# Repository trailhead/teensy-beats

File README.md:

# teensy-beats
Teensy Beats Shield

An all-in-one, made to hack step sequencer built around the Teensy platform with LiPo charging, touch TFT, encoders, buttons, and RGB leds.

Project build log and photos here:
https://hackaday.io/project/161127-teensy-beats-shield

...

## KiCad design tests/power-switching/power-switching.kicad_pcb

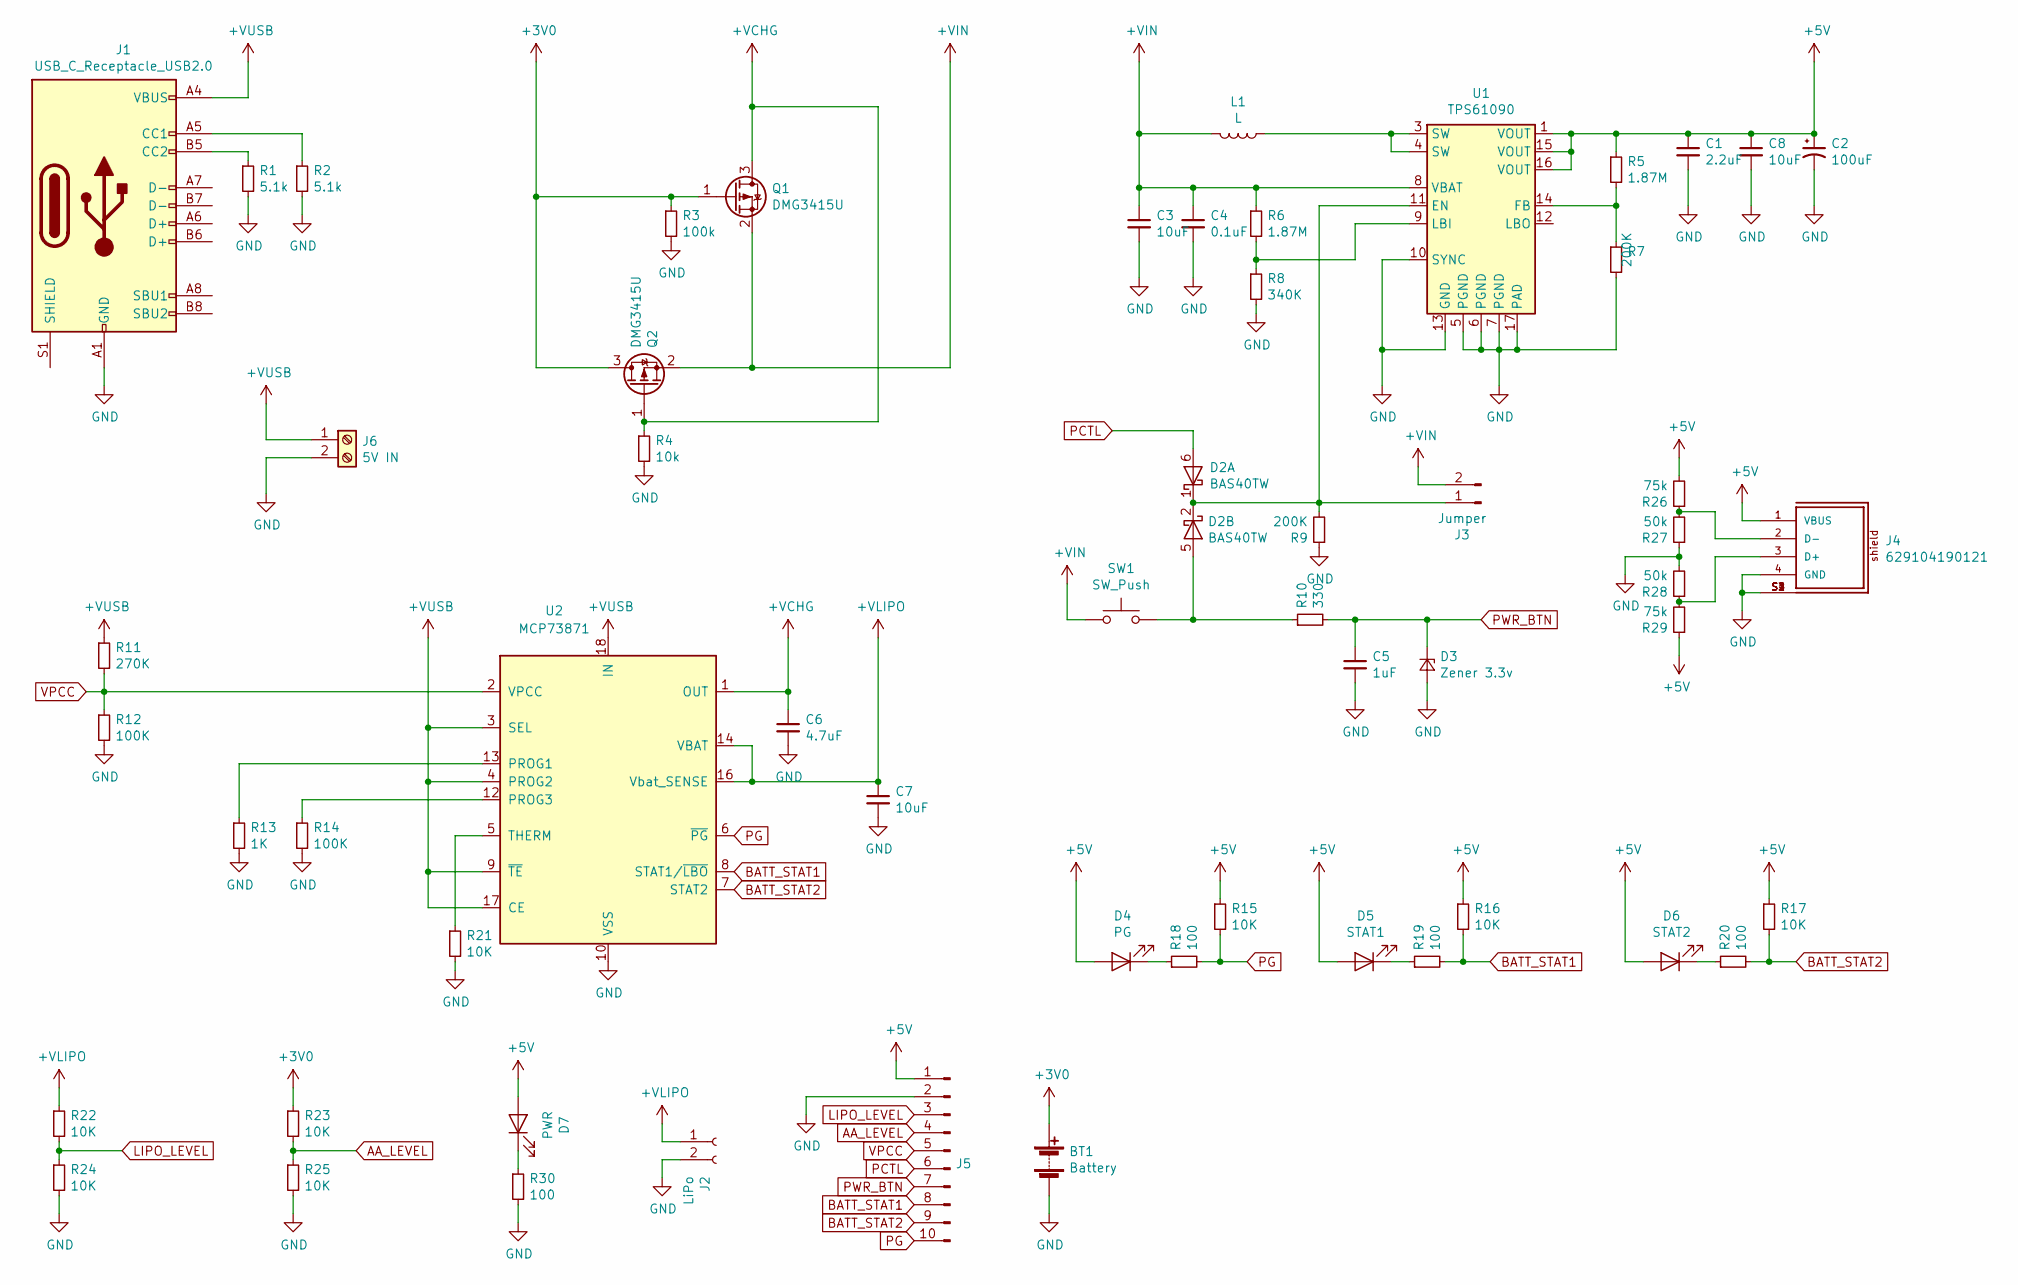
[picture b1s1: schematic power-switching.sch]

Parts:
BT1: Battery; BatteryHolder_Keystone_2462_2xAA
C1: 2.2uF; C_0805_2012Metric
C2: 100uF; CP_Elec_5x5.3
C3, C8: 10uF; C_1206_3216Metric
C4: 0.1uF; C_0805_2012Metric
C5: 1uF; C_0805_2012Metric
C6: 4.7uF; C_0805_2012Metric
C7: 10uF; C_0805_2012Metric
D2: BAS40TW; SOT-363_SC-70-6
D3: Zener 3.3v; D_SOD-323_HandSoldering
D4: PG; LED_0805_2012Metric
D5: STAT1; LED_0805_2012Metric
D6: STAT2; LED_0805_2012Metric
D7: PWR; LED_0805_2012Metric
J1: USB_C_Receptacle_USB2.0; MOLEX_105450-0101
J2: LiPo; JST_PH_S2B-PH-SM4-TB_1x02-1MP_P2.00mm_Horizontal
J3: Jumper; PinHeader_1x02_P2.54mm_Vertical
J4: 629104190121; PART-NUMBER 629104190121
J5: Conn_01x10_Male; PinHeader_1x10_P2.54mm_Vertical
J6: 5V IN; PhoenixContact_MSTBA_2,5_2-G_1x02_P5.00mm_Horizontal
L1: L; L_Taiyo-Yuden_NR-60xx
Q1, Q2: DMG3415U; SOT-23
R1, R2: 5.1k; R_0805_2012Metric
R3: 100k; R_0805_2012Metric
R4: 10k; R_0805_2012Metric
R5, R6: 1.87M; R_0805_2012Metric
R7, R9: 200K; R_0805_2012Metric
R8: 340K; R_0805_2012Metric
R10: 330; R_0805_2012Metric
R11: 270K; R_0805_2012Metric
R12, R14: 100K; R_0805_2012Metric
R13: 1K; R_0805_2012Metric
R15, R16, R17, R21, R22, R23, R24, R25: 10K; R_0805_2012Metric
R18, R19, R20, R30: 100; R_0805_2012Metric
R26, R29: 75k; R_0805_2012Metric
R27, R28: 50k; R_0805_2012Metric
SW1: SW_Push; SW_Tactile_SKHH_Angled
U1: TPS61090; QFN-16-1EP_4x4mm_P0.65mm_EP2.7x2.7mm_ThermalVias
U2: MCP73871; QFN-20-1EP_4x4mm_P0.5mm_EP2.6x2.6mm_ThermalVias

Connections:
+3V0: BT1.1 (+), Q1.1 (G), Q2.3 (D), R3.1, R23.1
+5V: C1.1, C2.1, C8.1, D4.2 (A), D5.2 (A), D6.2 (A), D7.2 (A), J4.1 (VBUS), J5.1, R5.1, R15.1, R16.1, R17.1, R26.2, R29.1, U1.1 (VOUT), U1.15 (VOUT), U1.16 (VOUT)
+VCHG: C6.1, Q1.3 (D), Q2.1 (G), R4.1, U2.1 (OUT), U2.20 (OUT)
+VIN: C3.1, C4.1, J3.2, L1.2, Q1.2 (S), Q2.2 (S), R6.1, SW1.2, U1.8 (VBAT)
+VLIPO: C7.1, J2.1, R22.1, U2.14 (VBAT), U2.15 (VBAT), U2.16 (Vbat_SENSE)
+VUSB: J1.A4 (VBUS), J1.A9 (VBUS), J1.B4 (VBUS), J1.B9 (VBUS), J6.1, R11.1, U2.3 (SEL), U2.4 (PROG2), U2.9 (~TE), U2.17 (CE), U2.18 (IN), U2.19 (IN)
AA_LEVEL: J5.4, R23.2, R25.1
BATT_STAT1: J5.8, R16.2, R19.2, U2.8 (STAT1/~LBO~)
BATT_STAT2: J5.9, R17.2, R20.2, U2.7 (STAT2)
GND: BT1.2 (-), C1.2, C2.2, C3.2, C4.2, C5.2, C6.2, C7.2, C8.2, D3.2 (A), J1.A1 (GND), J1.A12 (GND), J1.B1 (GND), J1.B12 (GND), J2.2, J4.4 (GND), J4.S1, J4.S2, J4.S3, J4.S4, J5.2, J6.2, R1.2, R2.2, R3.2, R4.2, R7.2, R8.2, R9.1, R12.2, R13.2, R14.2, R21.2, R24.2, R25.2, R27.1, R28.2, R30.2, U1.5 (PGND), U1.6 (PGND), U1.7 (PGND), U1.10 (SYNC), U1.13 (GND), U1.17 (PAD), U2.10 (VSS), U2.11 (VSS), U2.21 (VSS)
LIPO_LEVEL: J5.3, R22.2, R24.1
unnamed: D2.1 (K), D2.2 (K), J3.1, R9.2, U1.11 (EN)
unnamed: D2.5 (A), R10.1, SW1.1
unnamed: D4.1 (K), R18.1
unnamed: D5.1 (K), R19.1
unnamed: D6.1 (K), R20.1
unnamed: D7.1 (K), R30.1
unnamed: J1.A5 (CC1), R2.1
unnamed: J1.B5 (CC2), R1.1
unnamed: J4.2 (D-), R26.1, R27.2
unnamed: J4.3 (D+), R28.1, R29.2
unnamed: L1.1, U1.3 (SW), U1.4 (SW)
unnamed: R5.2, R7.1, U1.14 (FB)
unnamed: R6.2, R8.1, U1.9 (LBI)
unnamed: R13.1, U2.13 (PROG1)
unnamed: R14.1, U2.12 (PROG3)
unnamed: R21.1, U2.5 (THERM)
PCTL: D2.6 (A), J5.6
PG: J5.10, R15.2, R18.2, U2.6 (~PG~)
PWR_BTN: C5.1, D3.1 (K), J5.7, R10.2
VPCC: J5.5, R11.2, R12.1, U2.2 (VPCC)

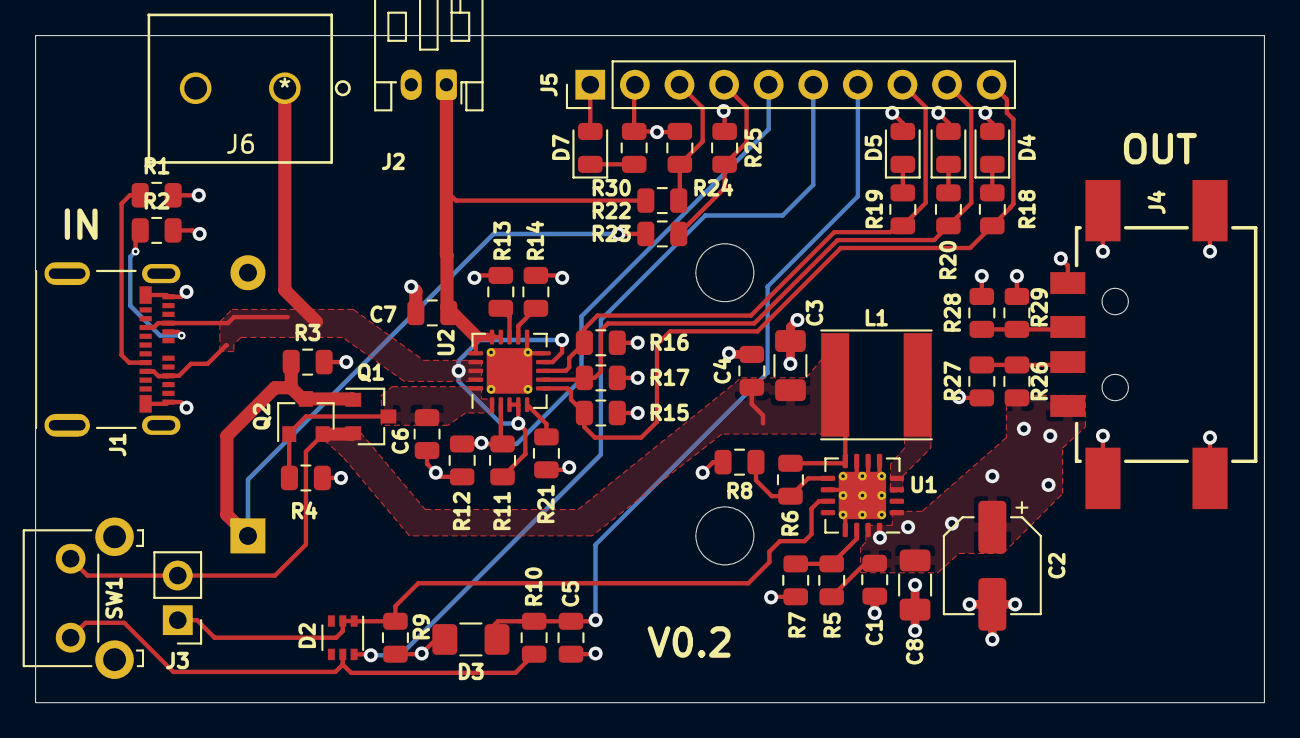
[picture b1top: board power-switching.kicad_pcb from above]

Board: 4 copper layers, 70.0 x 38.0 mm, 57 parts (1 on the bottom side), 31 nets.

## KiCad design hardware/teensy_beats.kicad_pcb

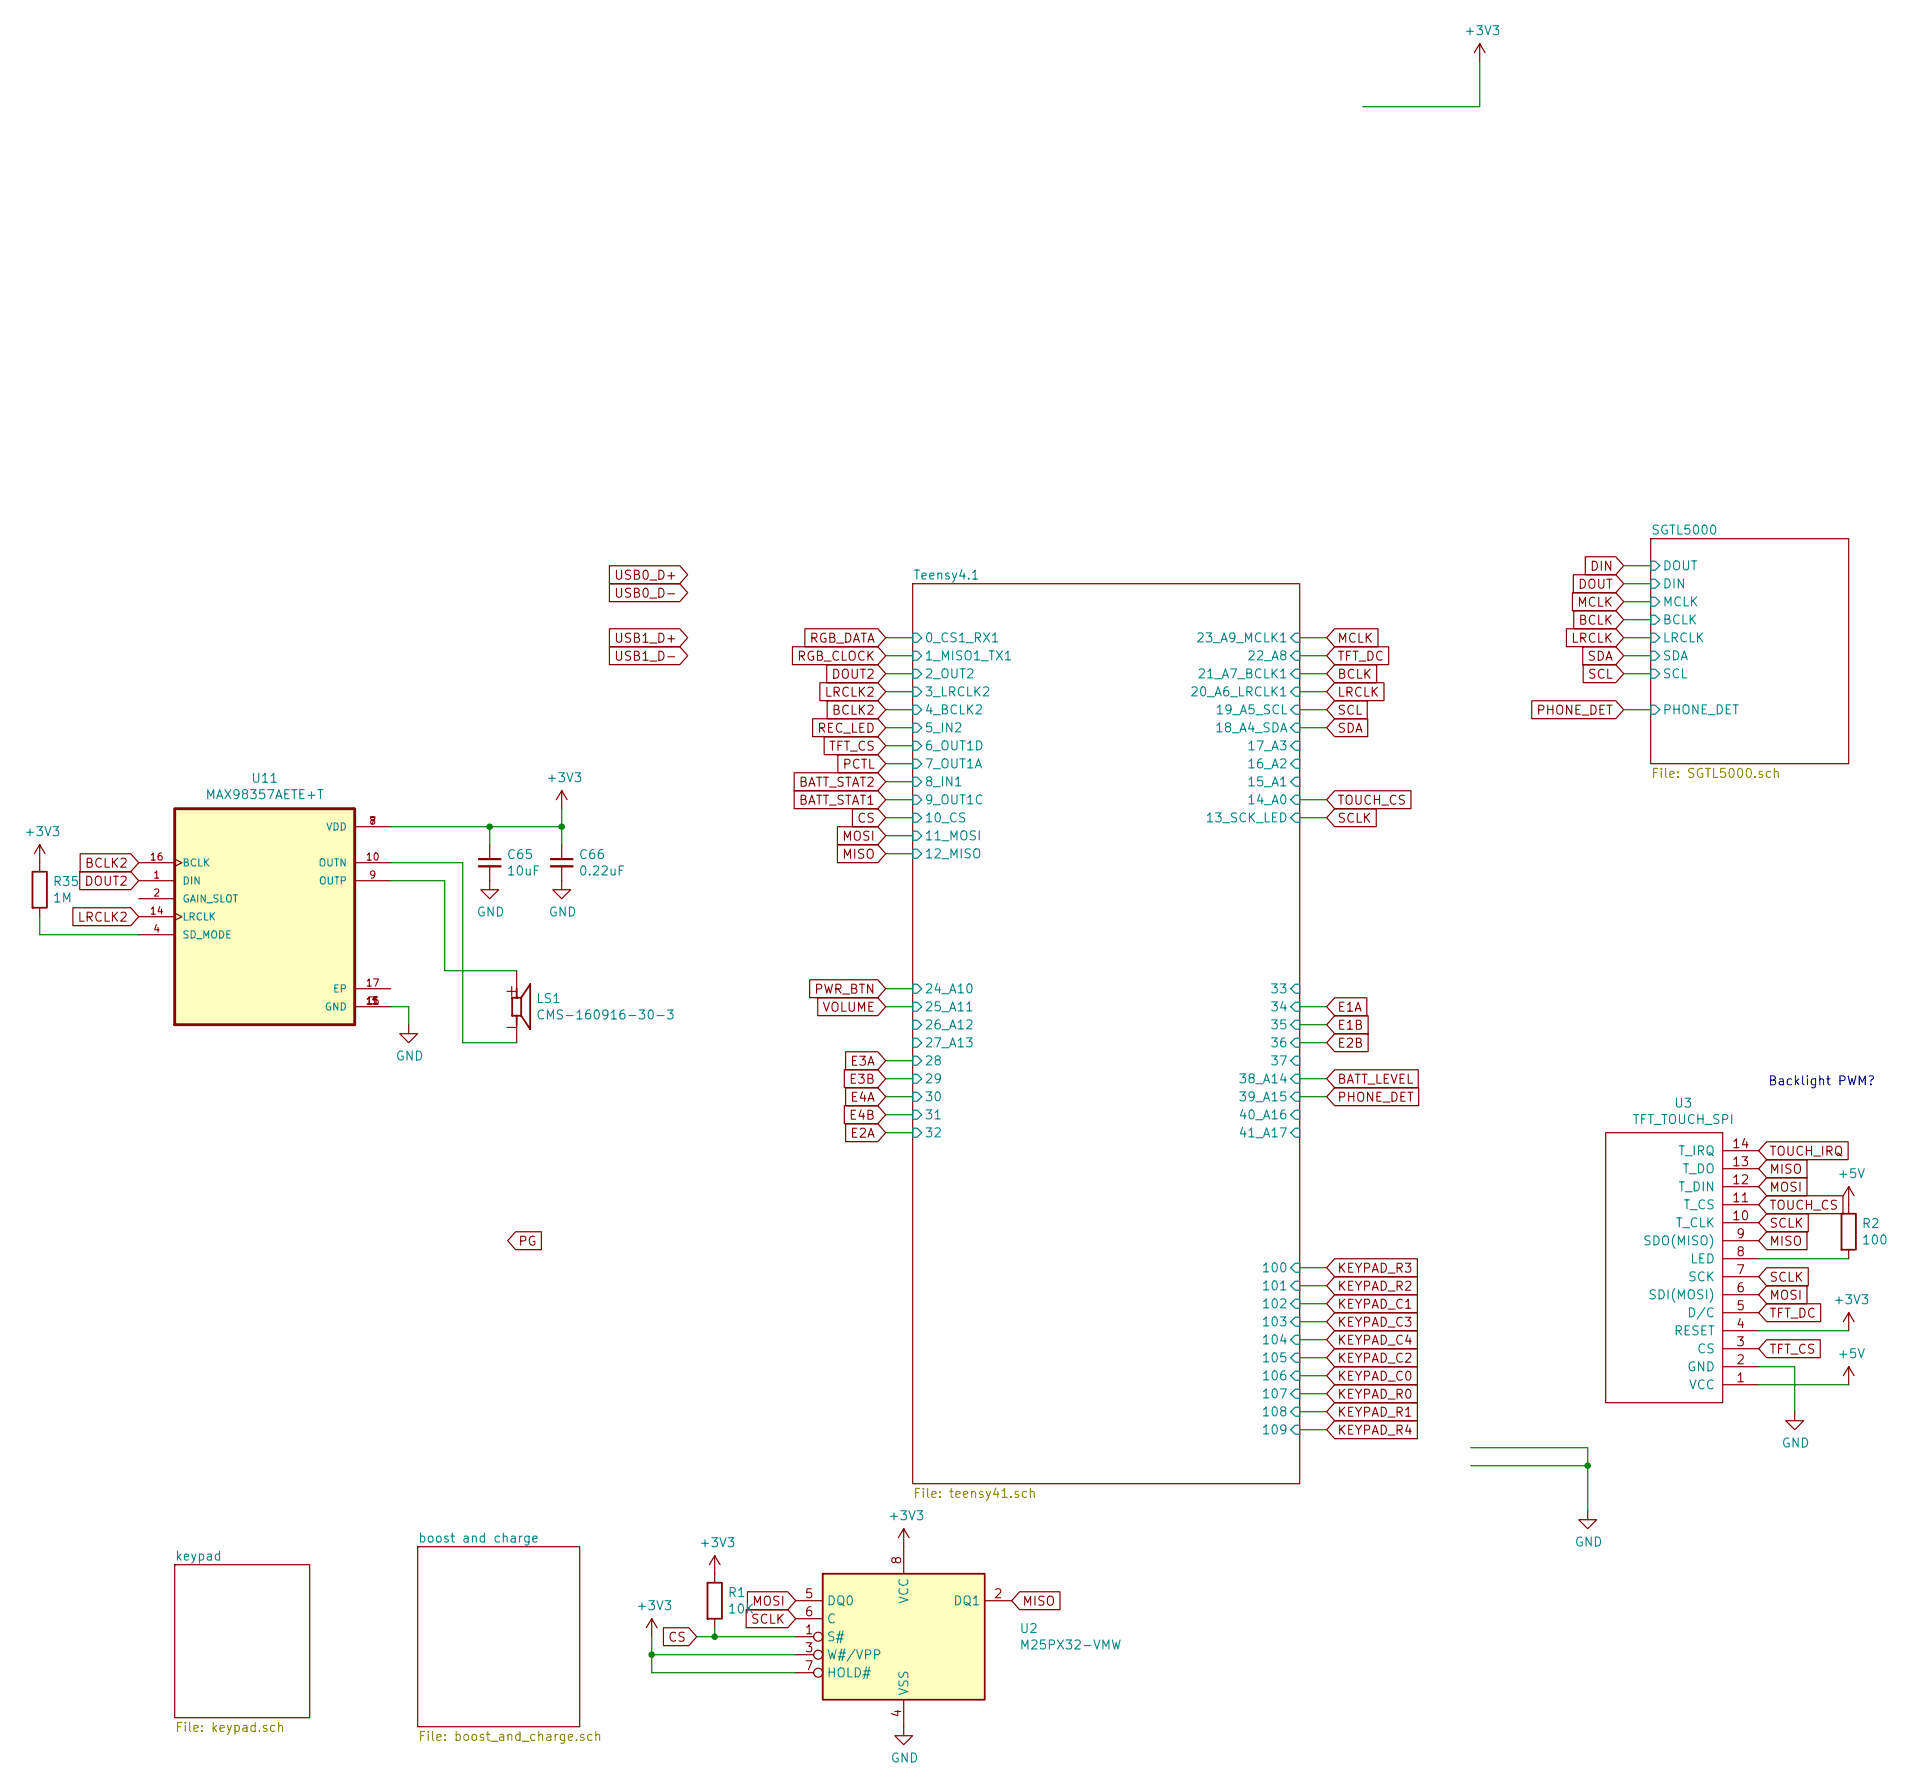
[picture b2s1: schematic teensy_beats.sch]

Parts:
C65: 10uF; C_0603_1608Metric
C66: 0.22uF; C_0402_1005Metric
LS1: CMS-160916-30-3; SPKR_CMS-160916-30-3; PARTREV 1.01
R1: 10K; R_0402_1005Metric
R2: 100; R_0402_1005Metric
R35: 1M; R_0402_1005Metric
U2: M25PX32-VMW; SOIC-8-N
U3: TFT_TOUCH_SPI; 2.4inTFT_TOUCH_SPI
U11: MAX98357AETE+T; QFN50P300X300X80-17N

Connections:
+3V3: C65.1, C66.1, R1.1, R35.1, U2.3 (W#/VPP), U2.7 (HOLD#), U2.8 (VCC), U3.4 (RESET), U11.7 (VDD), U11.8 (VDD); also elsewhere on the board
+5V: R2.1, U3.1 (VCC); also elsewhere on the board
BCLK2: U11.16 (BCLK); also elsewhere on the board
CS: R1.2, U2.1 (S#); also elsewhere on the board
DOUT2: U11.1 (DIN); also elsewhere on the board
GND: C65.2, C66.2, U2.4 (VSS), U3.2 (GND), U11.3 (GND), U11.11 (GND), U11.15 (GND); also elsewhere on the board
LRCLK2: U11.14 (LRCLK); also elsewhere on the board
MISO: U2.2 (DQ1), U3.9 (SDO(MISO)), U3.13 (T_DO); also elsewhere on the board
MOSI: U2.5 (DQ0), U3.6 (SDI(MOSI)), U3.12 (T_DIN); also elsewhere on the board
unnamed: LS1.N, U11.10 (OUTN)
unnamed: LS1.P, U11.9 (OUTP)
unnamed: R2.2, U3.8 (LED)
unnamed: R35.2, U11.4 (SD_MODE)
SCLK: U2.6 (C), U3.7 (SCK), U3.10 (T_CLK); also elsewhere on the board
TFT_CS: U3.3 (CS); also elsewhere on the board
TFT_DC: U3.5 (D/C); also elsewhere on the board
TOUCH_CS: U3.11 (T_CS); also elsewhere on the board
TOUCH_IRQ: U3.14 (T_IRQ)

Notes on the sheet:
Backlight PWM?

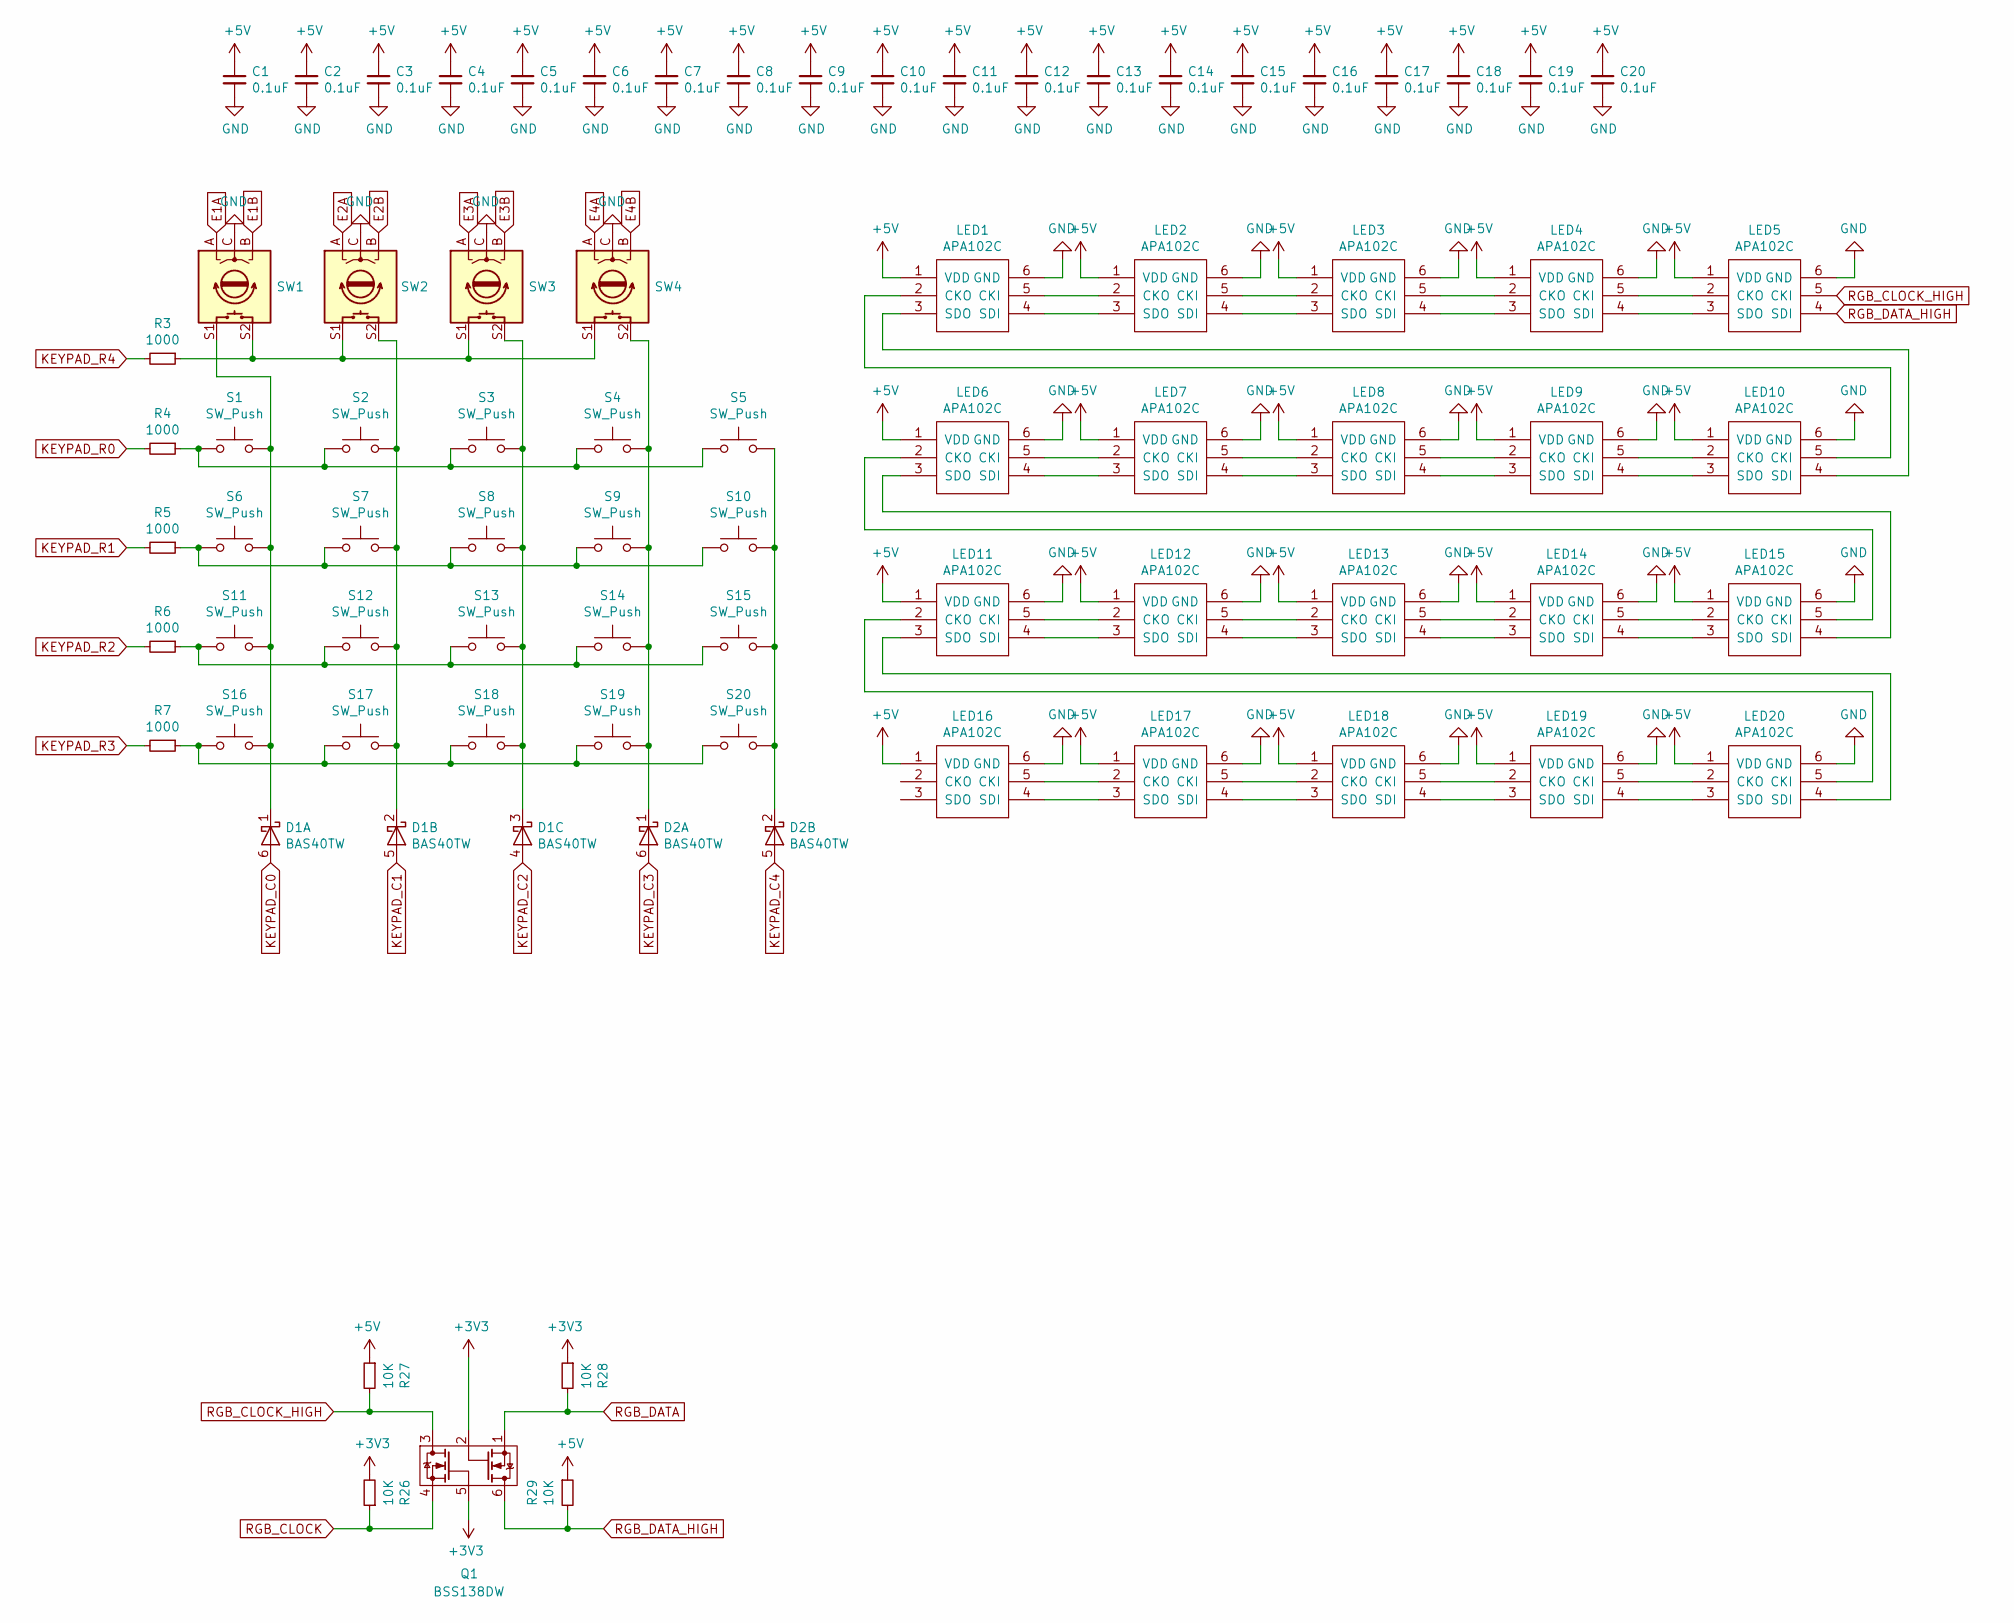
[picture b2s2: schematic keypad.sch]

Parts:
C1, C2, C3, C4, C5, C6, C7, C8, C9, C10, C11, C12, C13, C14, C15, C16, C17, C18, C19, C20: 0.1uF; C_0402_1005Metric
D1, D2: BAS40TW; SOT-363_SC-70-6
LED1, LED2, LED3, LED4, LED5, LED6, LED7, LED8, LED9, LED10, LED11, LED12, LED13, LED14, LED15, LED16, LED17, LED18, LED19, LED20: APA102C; APA102C-2020
Q1: BSS138DW; SOT-363_SC-70-6
R3, R4, R5, R6, R7: 1000; R_0402_1005Metric
R26, R27, R28, R29: 10K; R_0402_1005Metric
S1, S2, S3, S4, S5, S6, S7, S8, S9, S10, S11, S12, S13, S14, S15, S16, S17, S18, S19, S20: SW_Push; SW_SPST_EVQQ2
SW1, SW2, SW3, SW4: Rotary_Encoder_Switch; Bourns-SMD-Encoder

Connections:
+3V3: Q1.2 (G1), Q1.5 (G2), R26.2, R28.1; also elsewhere on the board
+5V: C1.1, C2.1, C3.1, C4.1, C5.1, C6.1, C7.1, C8.1, C9.1, C10.1, C11.1, C12.1, C13.1, C14.1, C15.1, C16.1, C17.1, C18.1, C19.1, C20.1, LED1.1 (VDD), LED2.1 (VDD), LED3.1 (VDD), LED4.1 (VDD), LED5.1 (VDD), LED6.1 (VDD), LED7.1 (VDD), LED8.1 (VDD), LED9.1 (VDD), LED10.1 (VDD), LED11.1 (VDD), LED12.1 (VDD), LED13.1 (VDD), LED14.1 (VDD), LED15.1 (VDD), LED16.1 (VDD), LED17.1 (VDD), LED18.1 (VDD), LED19.1 (VDD), LED20.1 (VDD), R27.1, R29.1; also elsewhere on the board
E1A: SW1.A; also elsewhere on the board
E1B: SW1.B; also elsewhere on the board
E2A: SW2.A; also elsewhere on the board
E2B: SW2.B; also elsewhere on the board
E3A: SW3.A; also elsewhere on the board
E3B: SW3.B; also elsewhere on the board
E4A: SW4.A; also elsewhere on the board
E4B: SW4.B; also elsewhere on the board
GND: C1.2, C2.2, C3.2, C4.2, C5.2, C6.2, C7.2, C8.2, C9.2, C10.2, C11.2, C12.2, C13.2, C14.2, C15.2, C16.2, C17.2, C18.2, C19.2, C20.2, LED1.6 (GND), LED2.6 (GND), LED3.6 (GND), LED4.6 (GND), LED5.6 (GND), LED6.6 (GND), LED7.6 (GND), LED8.6 (GND), LED9.6 (GND), LED10.6 (GND), LED11.6 (GND), LED12.6 (GND), LED13.6 (GND), LED14.6 (GND), LED15.6 (GND), LED16.6 (GND), LED17.6 (GND), LED18.6 (GND), LED19.6 (GND), LED20.6 (GND), SW1.C, SW2.C, SW3.C, SW4.C; also elsewhere on the board
KEYPAD_C0: D1.6 (A); also elsewhere on the board
KEYPAD_C1: D1.5 (A); also elsewhere on the board
KEYPAD_C2: D1.4 (A); also elsewhere on the board
KEYPAD_C3: D2.6 (A); also elsewhere on the board
KEYPAD_C4: D2.5 (A); also elsewhere on the board
KEYPAD_R0: R4.2; also elsewhere on the board
KEYPAD_R1: R5.2; also elsewhere on the board
KEYPAD_R2: R6.2; also elsewhere on the board
KEYPAD_R3: R7.2; also elsewhere on the board
KEYPAD_R4: R3.2; also elsewhere on the board
unnamed: D1.1 (K), S1.2, S6.2, S11.2, S16.2, SW1.S1
unnamed: D1.2 (K), S2.2, S7.2, S12.2, S17.2, SW2.S2
unnamed: D1.3 (K), S3.2, S8.2, S13.2, S18.2, SW3.S2
unnamed: D2.1 (K), S4.2, S9.2, S14.2, S19.2, SW4.S2
unnamed: D2.2 (K), S5.2, S10.2, S15.2, S20.2
unnamed: LED1.2 (CKO), LED10.5 (CKI)
unnamed: LED1.3 (SDO), LED10.4 (SDI)
unnamed: LED1.4 (SDI), LED2.3 (SDO)
unnamed: LED1.5 (CKI), LED2.2 (CKO)
unnamed: LED2.4 (SDI), LED3.3 (SDO)
unnamed: LED2.5 (CKI), LED3.2 (CKO)
unnamed: LED3.4 (SDI), LED4.3 (SDO)
unnamed: LED3.5 (CKI), LED4.2 (CKO)
unnamed: LED4.4 (SDI), LED5.3 (SDO)
unnamed: LED4.5 (CKI), LED5.2 (CKO)
unnamed: LED6.4 (SDI), LED7.3 (SDO)
unnamed: LED6.5 (CKI), LED7.2 (CKO)
unnamed: LED7.4 (SDI), LED8.3 (SDO)
unnamed: LED7.5 (CKI), LED8.2 (CKO)
unnamed: LED8.4 (SDI), LED9.3 (SDO)
unnamed: LED8.5 (CKI), LED9.2 (CKO)
unnamed: LED9.5 (CKI), LED10.2 (CKO)
unnamed: LED9.4 (SDI), LED10.3 (SDO)
unnamed: LED11.2 (CKO), LED20.5 (CKI)
unnamed: LED11.3 (SDO), LED20.4 (SDI)
unnamed: LED11.4 (SDI), LED12.3 (SDO)
unnamed: LED11.5 (CKI), LED12.2 (CKO)
unnamed: LED12.4 (SDI), LED13.3 (SDO)
unnamed: LED12.5 (CKI), LED13.2 (CKO)
unnamed: LED13.4 (SDI), LED14.3 (SDO)
unnamed: LED13.5 (CKI), LED14.2 (CKO)
unnamed: LED14.4 (SDI), LED15.3 (SDO)
unnamed: LED14.5 (CKI), LED15.2 (CKO)
unnamed: LED6.3 (SDO), LED15.4 (SDI)
unnamed: LED6.2 (CKO), LED15.5 (CKI)
unnamed: LED16.4 (SDI), LED17.3 (SDO)
unnamed: LED16.5 (CKI), LED17.2 (CKO)
unnamed: LED17.4 (SDI), LED18.3 (SDO)
unnamed: LED17.5 (CKI), LED18.2 (CKO)
unnamed: LED18.4 (SDI), LED19.3 (SDO)
unnamed: LED18.5 (CKI), LED19.2 (CKO)
unnamed: LED19.4 (SDI), LED20.3 (SDO)
unnamed: LED19.5 (CKI), LED20.2 (CKO)
unnamed: R3.1, SW1.S2, SW2.S1, SW3.S1, SW4.S1
unnamed: R4.1, S1.1, S2.1, S3.1, S4.1, S5.1
unnamed: R5.1, S6.1, S7.1, S8.1, S9.1, S10.1
unnamed: R6.1, S11.1, S12.1, S13.1, S14.1, S15.1
unnamed: R7.1, S16.1, S17.1, S18.1, S19.1, S20.1
RGB_CLOCK: Q1.4 (S2), R26.1; also elsewhere on the board
RGB_CLOCK_HIGH: LED5.5 (CKI), Q1.3 (D2), R27.2
RGB_DATA: Q1.1 (S1), R28.2; also elsewhere on the board
RGB_DATA_HIGH: LED5.4 (SDI), Q1.6 (D1), R29.2

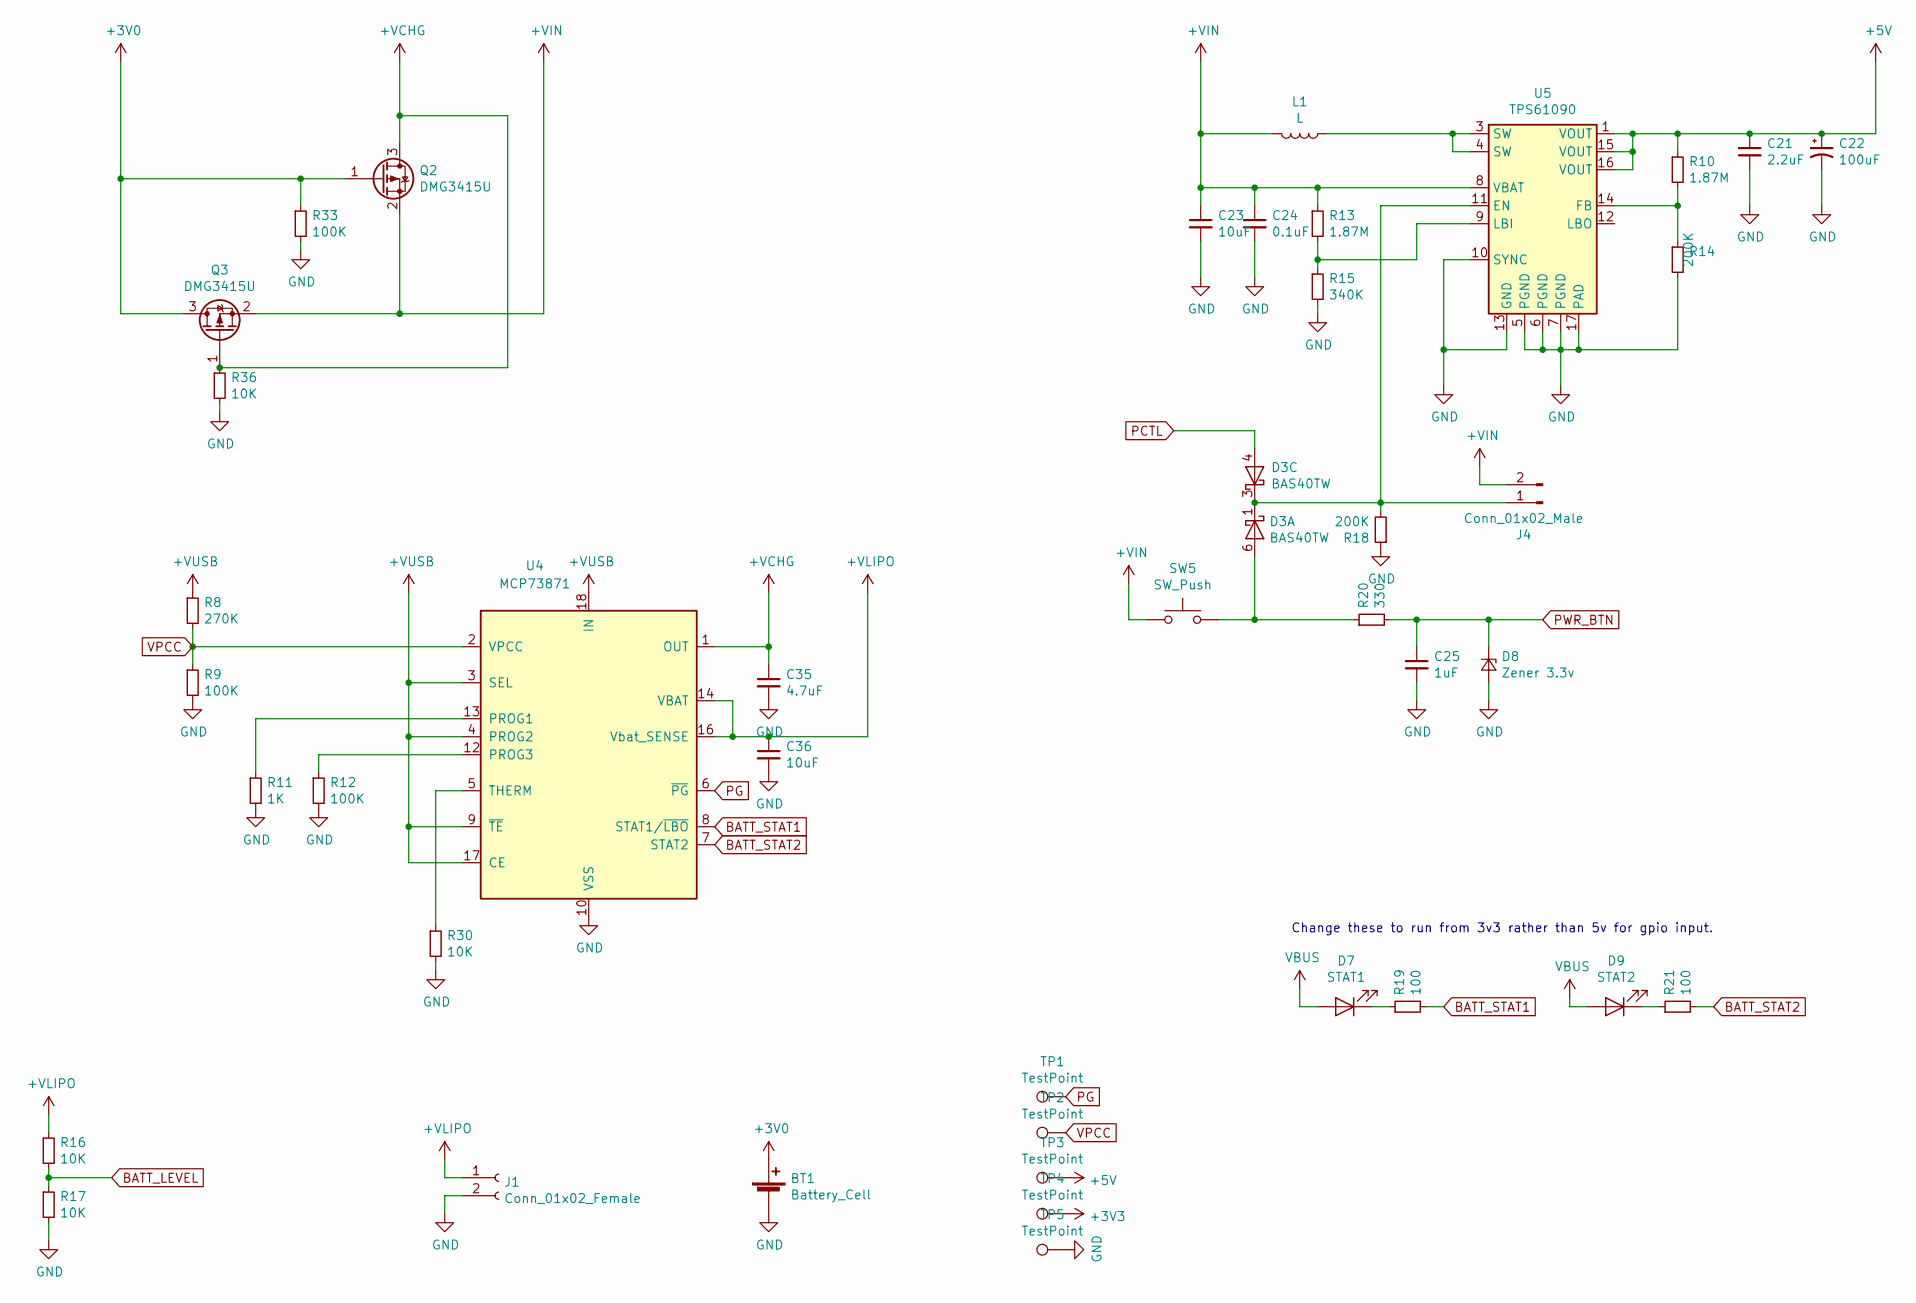
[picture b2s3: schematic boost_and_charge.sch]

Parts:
BT1: Battery_Cell; BatteryHolder_Keystone_2462_2xAA
C21: 2.2uF; C_0805_2012Metric
C22: 100uF; C_1210_3225Metric
C23, C36: 10uF; C_0805_2012Metric
C24: 0.1uF; C_0402_1005Metric
C25: 1uF; C_0805_2012Metric
C35: 4.7uF; C_0805_2012Metric
D3: BAS40TW; SOT-363_SC-70-6
D7: STAT1; LED_0805
D8: Zener 3.3v; D_SOD-323
D9: STAT2; LED_0805
J1: Conn_01x02_Female; JST_PH_S2B-PH-K_02x2.00mm_Angled
J4: Conn_01x02_Male; Pin_Header_Straight_1x02_Pitch1.27mm
L1: L; L_Taiyo-Yuden_NR-60xx
Q2, Q3: DMG3415U; SOT-23
R8: 270K; R_0402_1005Metric
R9, R12, R33: 100K; R_0402_1005Metric
R10, R13: 1.87M; R_0402_1005Metric
R11: 1K; R_0402_1005Metric
R14, R18: 200K; R_0402_1005Metric
R15: 340K; R_0402_1005Metric
R16, R17, R30, R36: 10K; R_0402_1005Metric
R19, R21: 100; R_0402_1005Metric
R20: 330; R_0402_1005Metric
SW5: SW_Push; SW_Tactile_SKHH_Angled
TP1, TP2, TP3, TP4, TP5: TestPoint; TestPoint1mm
U4: MCP73871; QFN-20-1EP_4x4mm_Pitch0.5mm
U5: TPS61090; QFN-16-1EP_4x4mm_Pitch0.65mm

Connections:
+3V0: BT1.1 (+), Q2.1 (G), Q3.3 (D), R33.1
+3V3: TP4.1; also elsewhere on the board
+5V: C21.1, C22.1, R10.1, TP3.1, U5.1 (VOUT), U5.15 (VOUT), U5.16 (VOUT); also elsewhere on the board
+VCHG: C35.1, Q2.3 (D), Q3.1 (G), R36.1, U4.1 (OUT), U4.20 (OUT)
+VIN: C23.1, C24.1, J4.2, L1.2, Q2.2 (S), Q3.2 (S), R13.1, SW5.2, U5.8 (VBAT)
+VLIPO: C36.1, J1.1, R16.1, U4.14 (VBAT), U4.15 (VBAT), U4.16 (Vbat_SENSE)
+VUSB: R8.1, U4.3 (SEL), U4.4 (PROG2), U4.9 (~TE), U4.17 (CE), U4.18 (IN), U4.19 (IN); also elsewhere on the board
BATT_LEVEL: R16.2, R17.1; also elsewhere on the board
BATT_STAT1: R19.2, U4.8 (STAT1/~LBO~); also elsewhere on the board
BATT_STAT2: R21.2, U4.7 (STAT2); also elsewhere on the board
GND: BT1.2 (-), C21.2, C22.2, C23.2, C24.2, C25.2, C35.2, C36.2, D8.2 (A), J1.2, R9.2, R11.2, R12.2, R14.2, R15.2, R17.2, R18.1, R30.2, R33.2, R36.2, TP5.1, U4.10 (VSS), U4.11 (VSS), U4.21 (VSS), U5.5 (PGND), U5.6 (PGND), U5.7 (PGND), U5.10 (SYNC), U5.13 (GND), U5.17 (PAD); also elsewhere on the board
unnamed: D3.1 (K), D3.3 (K), J4.1, R18.2, U5.11 (EN)
unnamed: D3.6 (A), R20.1, SW5.1
unnamed: D7.1 (K), R19.1
unnamed: D9.1 (K), R21.1
unnamed: L1.1, U5.3 (SW), U5.4 (SW)
unnamed: R10.2, R14.1, U5.14 (FB)
unnamed: R11.1, U4.13 (PROG1)
unnamed: R12.1, U4.12 (PROG3)
unnamed: R13.2, R15.1, U5.9 (LBI)
unnamed: R30.1, U4.5 (THERM)
PCTL: D3.4 (A); also elsewhere on the board
PG: TP1.1, U4.6 (~PG~)
PWR_BTN: C25.1, D8.1 (K), R20.2; also elsewhere on the board
VBUS: D7.2 (A), D9.2 (A)
VPCC: R8.2, R9.1, TP2.1, U4.2 (VPCC)

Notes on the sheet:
Change these to run from 3v3 rather than 5v for gpio input.

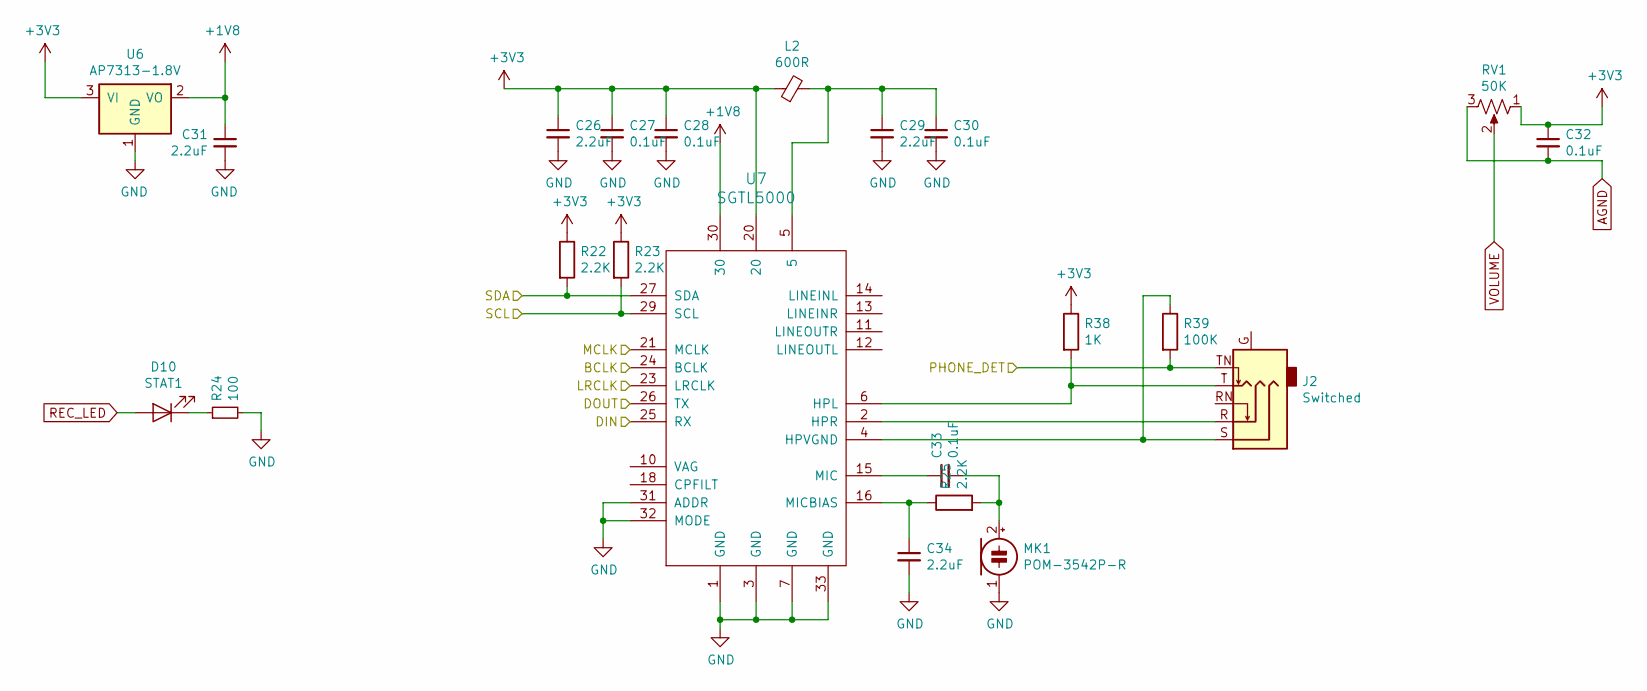
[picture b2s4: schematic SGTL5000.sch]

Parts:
C26, C29, C31, C34: 2.2uF; C_0805_2012Metric
C27, C28, C30, C32, C33: 0.1uF; C_0402_1005Metric
D10: STAT1; LED_0805
J2: Switched; SJ1-3525N
L2: 600R; L_0805
MK1: POM-3542P-R; AOM-6738P-R
R22, R23, R25: 2.2K; R_0402_1005Metric
R24: 100; R_0402_1005Metric
R38: 1K; R_0402_1005Metric
R39: 100K; R_0402_1005Metric
RV1: 50K; RV100F-30-4K1-B50K
U6: AP7313-1.8V; SOT-23-3
U7: SGTL5000; QFN-32-1EP_5x5mm_Pitch0.5mm

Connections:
+1V8: C31.1, U6.2 (VO), U7.30
+3V3: C26.1, C27.1, C28.1, C32.1, L2.1, R22.1, R23.1, R38.1, RV1.1, U6.3 (VI), U7.20; also elsewhere on the board
AGND: C32.2, RV1.3
BCLK: U7.24 (BCLK); also elsewhere on the board
DIN: U7.26 (TX)
DOUT: U7.25 (RX)
GND: C26.2, C27.2, C28.2, C29.2, C30.2, C31.2, C34.2, MK1.1 (-), R24.2, U6.1 (GND), U7.1 (GND), U7.3 (GND), U7.7 (GND), U7.31 (ADDR), U7.32 (MODE), U7.33 (GND); also elsewhere on the board
LRCLK: U7.23 (LRCLK); also elsewhere on the board
MCLK: U7.21 (MCLK); also elsewhere on the board
unnamed: C29.1, C30.1, L2.2, U7.5
unnamed: C33.1, U7.15 (MIC)
unnamed: C33.2, MK1.2 (+), R25.2
unnamed: C34.1, R25.1, U7.16 (MICBIAS)
unnamed: D10.1 (K), R24.1
unnamed: J2.R, U7.2 (HPR)
unnamed: J2.S, R39.1, U7.4 (HPVGND)
unnamed: J2.T, R38.2, U7.6 (HPL)
PHONE_DET: J2.TN, R39.2; also elsewhere on the board
REC_LED: D10.2 (A); also elsewhere on the board
SCL: R23.2, U7.29 (SCL); also elsewhere on the board
SDA: R22.2, U7.27 (SDA); also elsewhere on the board
VOLUME: RV1.2; also elsewhere on the board

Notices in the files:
hardware/teensy_beats.kicad_pcb:
(C) 2018 Chris Miller
parts and their libraries:
Copyright 2016 Accelerated Designs. All rights reserved.
